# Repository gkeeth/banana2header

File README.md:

# Banana to Pinheader Adapter

Convenience board for connecting banana cables (e.g. from a power supply) to a
Molex SL pinheader for interfacing with projects. Simplifies powering projects
from a bench power supply.

Provides three connections: V_A, V_B, and GND. These are intended for positive
and negative supplies with a center ground but they can be used arbitrarily.

Also provides testpoints for all three connections.

## BOM
| Refdes | Description | Manufacturer PN | Comments |
| ------ | ----------- | --------------- | -------- |
| J1, J2, J3 | Banana Jack | Caltest CT3151 | pick color as desired |
| J4 | Molex SL connector | Molex 70543-0002 | This could be basically any 0.1" header; it doesn't have to be Molex SL. |
| J5, J6 | Testpoints | n/a | use generic 0.1" breakaway header, or omit. |

## License
This work is licensed under a [Creative Commons Attribution-ShareAlike 4.0
International License][cc-by-sa].

[![CC BY-SA 4.0][cc-by-sa-image]][cc-by-sa]

[cc-by-sa]: http://creativecommons.org/licenses/by-sa/4.0/
[cc-by-sa-image]: https://licensebuttons.net/l/by-sa/4.0/88x31.png
[cc-by-sa-shield]: https://img.shields.io/badge/License-CC%20BY--SA%204.0-lightgrey.svg

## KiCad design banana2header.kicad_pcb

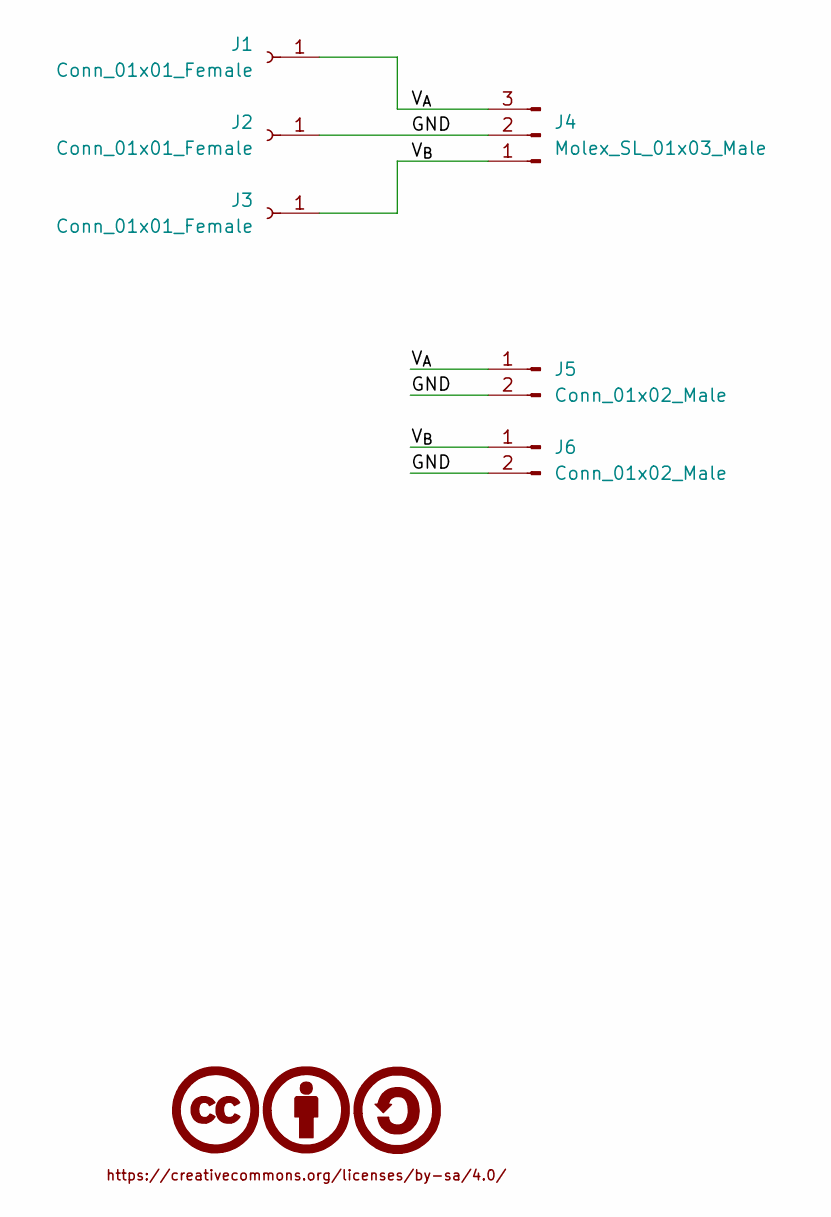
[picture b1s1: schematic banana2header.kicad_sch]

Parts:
J1, J2, J3: Conn_01x01_Female; CalTest_CT3151
J4: Molex_SL_01x03_Male; Molex_SL_A-70543-0002_1x03_P2.54mm_Vertical
J5, J6: Conn_01x02_Male; PinHeader_1x02_P2.54mm_Vertical
LOGO1: CC-BY-SA_0.33in; CC-BY-SA_SilkScreenTop_Small

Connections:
/GND: J2.1, J4.2, J5.2, J6.2
/V_{A}: J1.1, J4.3, J5.1
/V_{B}: J3.1, J4.1, J6.1

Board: 2 copper layers, 7 parts (1 on the bottom side), 3 nets, no tracks yet.

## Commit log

2022-08-28 initial commit (routing complete)
2022-08-28 add license decal
2022-08-28 add readme
2022-08-28 add picture
2022-08-28 add note about header alternatives
2022-08-28 save while generating gerbers
2022-08-28 ignore fab outputs
2022-08-28 add jlc order number string

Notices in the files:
banana2header.kicad_sch:
https://creativecommons.org/licenses/by-sa/4.0
